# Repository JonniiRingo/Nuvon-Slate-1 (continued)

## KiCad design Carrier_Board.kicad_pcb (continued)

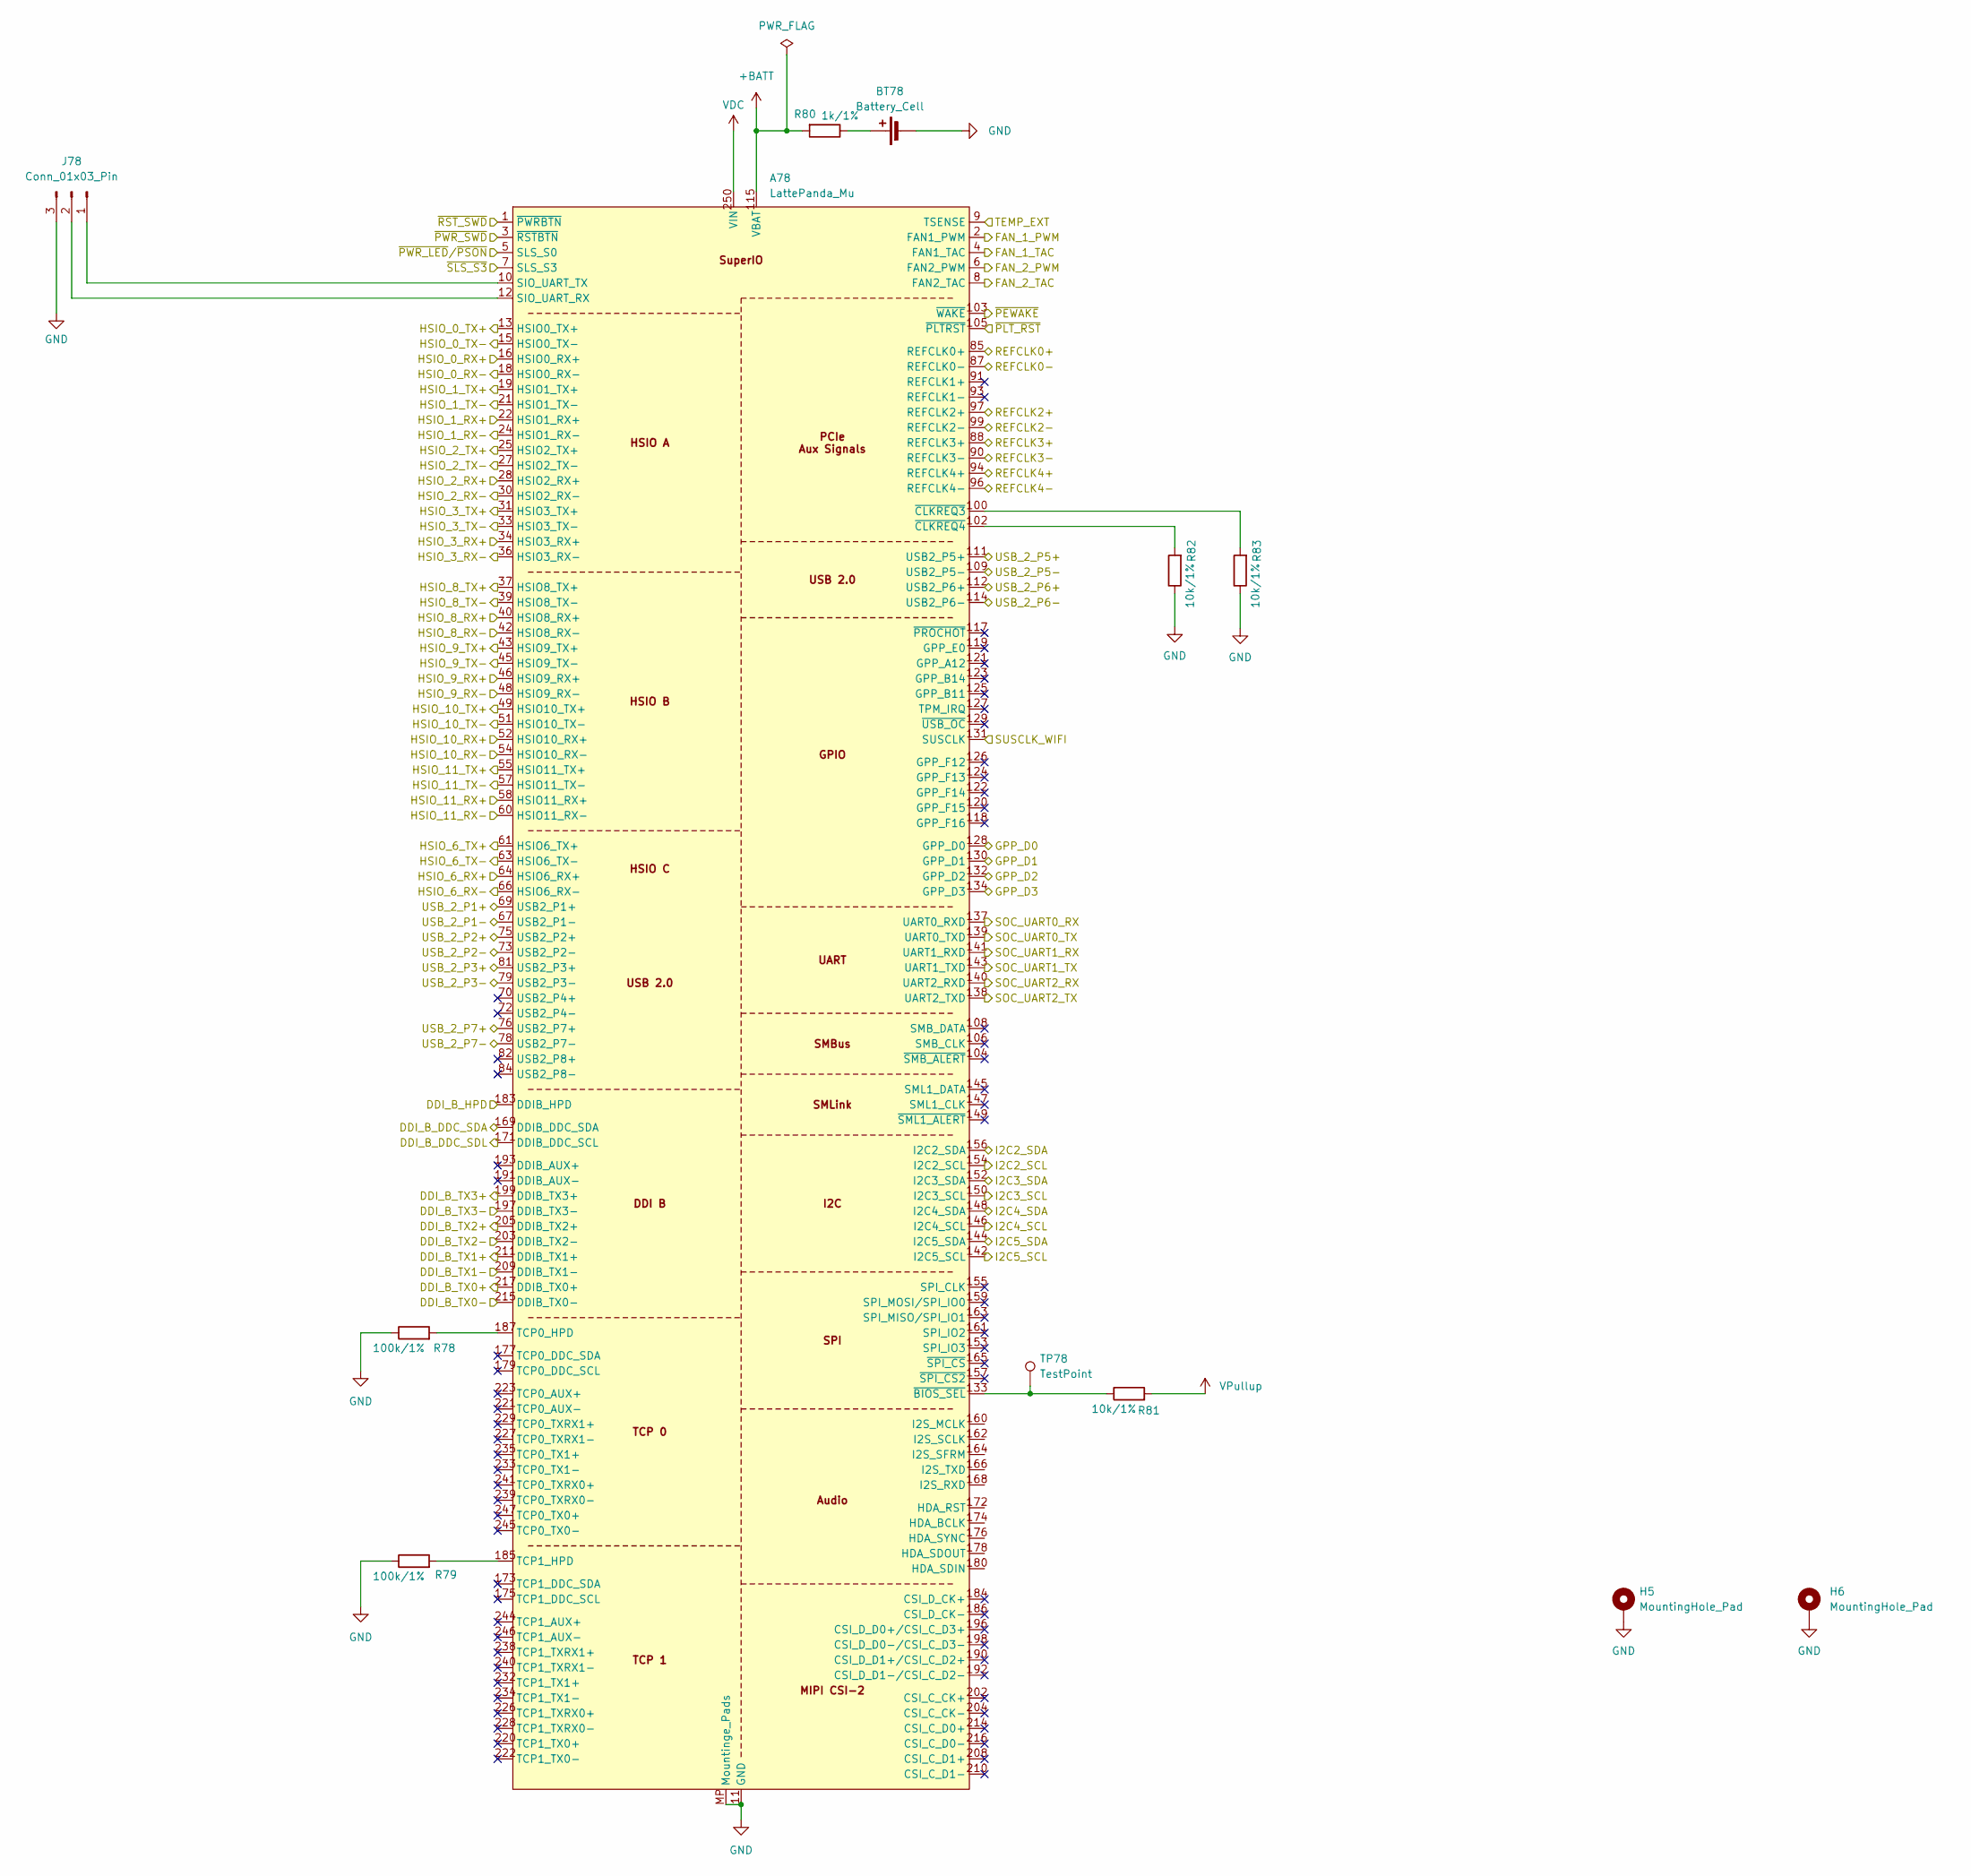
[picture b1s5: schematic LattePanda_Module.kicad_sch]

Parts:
A78: LattePanda_Mu; LattePanda_Module_H8.0mm_Horizontal
BT78: Battery_Cell; Battery_Holder_CR1220_S8411-45R
H5, H6: MountingHole_Pad; MountingHole_3mm_M2_Pad_TopOnly
J78: Conn_01x03_Pin; PinHeader_1x03_P2.54mm_Vertical
R78, R79: 100k/1%; R_0402_1005Metric
R80: 1k/1%; R_0402_1005Metric
R81, R82, R83: 10k/1%; R_0402_1005Metric
TP78: TestPoint; TestPoint_Pad_D1.5mm

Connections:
+BATT: A78.115 (VBAT), R80.2
/Fan/FAN_1_PWM: A78.4 (FAN1_TAC); also elsewhere on the board
/Fan/FAN_1_TAC: A78.2 (FAN1_PWM); also elsewhere on the board
/Fan/FAN_2_PWM: A78.8 (FAN2_TAC); also elsewhere on the board
/Fan/FAN_2_TAC: A78.6 (FAN2_PWM); also elsewhere on the board
/Fan/TEMP: A78.9 (TSENSE); also elsewhere on the board
/GPIO/GPP_D0: A78.128 (GPP_D0); also elsewhere on the board
/GPIO/GPP_D1: A78.130 (GPP_D1); also elsewhere on the board
/GPIO/GPP_D2: A78.132 (GPP_D2); also elsewhere on the board
/GPIO/GPP_D3: A78.134 (GPP_D3); also elsewhere on the board
/GPIO/I2C2_SCL: A78.154 (I2C2_SCL); also elsewhere on the board
/GPIO/I2C2_SDA: A78.156 (I2C2_SDA); also elsewhere on the board
/GPIO/I2C3_SCL: A78.150 (I2C3_SCL); also elsewhere on the board
/GPIO/I2C3_SDA: A78.152 (I2C3_SDA); also elsewhere on the board
/GPIO/I2C4_SCL: A78.146 (I2C4_SCL); also elsewhere on the board
/GPIO/I2C4_SDA: A78.148 (I2C4_SDA); also elsewhere on the board
/GPIO/I2C5_SCL: A78.142 (I2C5_SCL); also elsewhere on the board
/GPIO/I2C5_SDA: A78.144 (I2C5_SDA); also elsewhere on the board
/GPIO/SOC_UART0_RX: A78.137 (UART0_RXD); also elsewhere on the board
/GPIO/SOC_UART0_TX: A78.139 (UART0_TXD); also elsewhere on the board
/GPIO/SOC_UART1_RX: A78.141 (UART1_RXD); also elsewhere on the board
/GPIO/SOC_UART1_TX: A78.143 (UART1_TXD); also elsewhere on the board
/GPIO/SOC_UART2_RX: A78.140 (UART2_RXD); also elsewhere on the board
/GPIO/SOC_UART2_TX: A78.138 (UART2_TXD); also elsewhere on the board
/Gigabit Ethernet/GbE_PCIe_CLK+: A78.94 (REFCLK4+); also elsewhere on the board
/Gigabit Ethernet/GbE_PCIe_CLK-: A78.96 (REFCLK4-); also elsewhere on the board
/Gigabit Ethernet/GbE_PCIe_RX+: A78.64 (HSIO6_RX+); also elsewhere on the board
/Gigabit Ethernet/GbE_PCIe_RX-: A78.66 (HSIO6_RX-); also elsewhere on the board
/Gigabit Ethernet/GbE_PCIe_TX+: A78.61 (HSIO6_TX+); also elsewhere on the board
/Gigabit Ethernet/GbE_PCIe_TX-: A78.63 (HSIO6_TX-); also elsewhere on the board
/HDMI/DDI_B_HPD: A78.183 (DDIB_HPD); also elsewhere on the board
/HDMI/DDI_B_TX0+: A78.217 (DDIB_TX0+); also elsewhere on the board
/HDMI/DDI_B_TX0-: A78.215 (DDIB_TX0-); also elsewhere on the board
/HDMI/DDI_B_TX1+: A78.211 (DDIB_TX1+); also elsewhere on the board
/HDMI/DDI_B_TX1-: A78.209 (DDIB_TX1-); also elsewhere on the board
/HDMI/DDI_B_TX2+: A78.205 (DDIB_TX2+); also elsewhere on the board
/HDMI/DDI_B_TX2-: A78.203 (DDIB_TX2-); also elsewhere on the board
/HDMI/DDI_B_TX3+: A78.199 (DDIB_TX3+); also elsewhere on the board
/HDMI/DDI_B_TX3-: A78.197 (DDIB_TX3-); also elsewhere on the board
/HDMI/DDI_DDC_SCA: A78.169 (DDIB_DDC_SDA); also elsewhere on the board
/HDMI/DDI_DDC_SCL: A78.171 (DDIB_DDC_SCL); also elsewhere on the board
/LattePanda Module/HSIO_0_TX+: A78.13 (HSIO0_TX+); also elsewhere on the board
/LattePanda Module/HSIO_0_TX-: A78.15 (HSIO0_TX-); also elsewhere on the board
/LattePanda Module/HSIO_1_TX+: A78.19 (HSIO1_TX+); also elsewhere on the board
/LattePanda Module/HSIO_1_TX-: A78.21 (HSIO1_TX-); also elsewhere on the board
/LattePanda Module/HSIO_2_RX+: A78.28 (HSIO2_RX+); also elsewhere on the board
/LattePanda Module/HSIO_2_RX-: A78.30 (HSIO2_RX-); also elsewhere on the board
/LattePanda Module/HSIO_2_TX+: A78.25 (HSIO2_TX+); also elsewhere on the board
/LattePanda Module/HSIO_2_TX-: A78.27 (HSIO2_TX-); also elsewhere on the board
/LattePanda Module/HSIO_3_RX+: A78.34 (HSIO3_RX+); also elsewhere on the board
/LattePanda Module/HSIO_3_RX-: A78.36 (HSIO3_RX-); also elsewhere on the board
/LattePanda Module/HSIO_3_TX+: A78.31 (HSIO3_TX+); also elsewhere on the board
/LattePanda Module/HSIO_3_TX-: A78.33 (HSIO3_TX-); also elsewhere on the board
/LattePanda Module/HSIO_8_RX+: A78.40 (HSIO8_RX+); also elsewhere on the board
/LattePanda Module/HSIO_8_RX-: A78.42 (HSIO8_RX-); also elsewhere on the board
/LattePanda Module/HSIO_8_TX+: A78.37 (HSIO8_TX+); also elsewhere on the board
/LattePanda Module/HSIO_8_TX-: A78.39 (HSIO8_TX-); also elsewhere on the board
/LattePanda Module/HSIO_9_RX+: A78.46 (HSIO9_RX+); also elsewhere on the board
/LattePanda Module/HSIO_9_RX-: A78.48 (HSIO9_RX-); also elsewhere on the board
/LattePanda Module/HSIO_9_TX+: A78.43 (HSIO9_TX+); also elsewhere on the board
/LattePanda Module/HSIO_9_TX-: A78.45 (HSIO9_TX-); also elsewhere on the board
/LattePanda Module/HSIO_10_RX+: A78.52 (HSIO10_RX+); also elsewhere on the board
/LattePanda Module/HSIO_10_RX-: A78.54 (HSIO10_RX-); also elsewhere on the board
/LattePanda Module/HSIO_10_TX+: A78.49 (HSIO10_TX+); also elsewhere on the board
/LattePanda Module/HSIO_10_TX-: A78.51 (HSIO10_TX-); also elsewhere on the board
/LattePanda Module/HSIO_11_RX+: A78.58 (HSIO11_RX+); also elsewhere on the board
/LattePanda Module/HSIO_11_RX-: A78.60 (HSIO11_RX-); also elsewhere on the board
/LattePanda Module/HSIO_11_TX+: A78.55 (HSIO11_TX+); also elsewhere on the board
/LattePanda Module/HSIO_11_TX-: A78.57 (HSIO11_TX-); also elsewhere on the board
/LattePanda Module/REFCLK0+: A78.85 (REFCLK0+); also elsewhere on the board
/LattePanda Module/REFCLK0-: A78.87 (REFCLK0-); also elsewhere on the board
/LattePanda Module/REFCLK2+: A78.97 (REFCLK2+); also elsewhere on the board
/LattePanda Module/REFCLK2-: A78.99 (REFCLK2-); also elsewhere on the board
/LattePanda Module/REFCLK3+: A78.88 (REFCLK3+); also elsewhere on the board
/LattePanda Module/REFCLK3-: A78.90 (REFCLK3-); also elsewhere on the board
/LattePanda Module/SUSCLK_WIFI: A78.131 (SUSCLK); also elsewhere on the board
/LattePanda Module/USB_2_P6+: A78.112 (USB2_P6+)
/LattePanda Module/USB_2_P6-: A78.114 (USB2_P6-)
/LattePanda Module/USB_2_P7+: A78.76 (USB2_P7+); also elsewhere on the board
/LattePanda Module/USB_2_P7-: A78.78 (USB2_P7-); also elsewhere on the board
/LattePanda Module/~PWR_LED/~PSON: A78.5 (SLS_S0); also elsewhere on the board
/LattePanda Module/~PWR_SWD: A78.3 (~RSTBTN); also elsewhere on the board
/LattePanda Module/~RST_SWD: A78.1 (~PWRBTN); also elsewhere on the board
/USB 2.0 & 3.0/CON_USB1_D_N: A78.109 (USB2_P5-); also elsewhere on the board
/USB 2.0 & 3.0/CON_USB1_D_P: A78.111 (USB2_P5+); also elsewhere on the board
/USB 2.0 & 3.0/CON_USB2_D_N: A78.79 (USB2_P3-); also elsewhere on the board
/USB 2.0 & 3.0/CON_USB2_D_P: A78.81 (USB2_P3+); also elsewhere on the board
/USB 2.0 & 3.0/CON_USB3_D_N: A78.73 (USB2_P2-); also elsewhere on the board
/USB 2.0 & 3.0/CON_USB3_D_P: A78.75 (USB2_P2+); also elsewhere on the board
/USB 2.0 & 3.0/CON_USB3_SSRX_N: A78.18 (HSIO0_RX-); also elsewhere on the board
/USB 2.0 & 3.0/CON_USB3_SSRX_P: A78.16 (HSIO0_RX+); also elsewhere on the board
/USB 2.0 & 3.0/CON_USB4_D_N: A78.67 (USB2_P1-); also elsewhere on the board
/USB 2.0 & 3.0/CON_USB4_D_P: A78.69 (USB2_P1+); also elsewhere on the board
/USB 2.0 & 3.0/CON_USB4_SSRX_N: A78.24 (HSIO1_RX-); also elsewhere on the board
/USB 2.0 & 3.0/CON_USB4_SSRX_P: A78.22 (HSIO1_RX+); also elsewhere on the board
/~PLT_RST: A78.105 (~PLTRST); also elsewhere on the board
/~PWR_LED/~PSON: A78.7 (SLS_S3); also elsewhere on the board
/~WAKE: A78.103 (~WAKE); also elsewhere on the board
GND: A78.11 (GND), A78.14 (GND), A78.17 (GND), A78.20 (GND), A78.23 (GND), A78.26 (GND), A78.29 (GND), A78.32 (GND), A78.35 (GND), A78.38 (GND), A78.41 (GND), A78.44 (GND), A78.47 (GND), A78.50 (GND), A78.53 (GND), A78.56 (GND), A78.59 (GND), A78.62 (GND), A78.65 (GND), A78.68 (GND), A78.71 (GND), A78.74 (GND), A78.77 (GND), A78.80 (GND), A78.83 (GND), A78.86 (GND), A78.89 (GND), A78.92 (GND), A78.95 (GND), A78.98 (GND), A78.101 (GND), A78.107 (GND), A78.110 (GND), A78.113 (GND), A78.116 (GND), A78.135 (GND), A78.136 (GND), A78.151 (GND), A78.158 (GND), A78.167 (GND), A78.170 (GND), A78.181 (GND), A78.182 (GND), A78.188 (GND), A78.189 (GND), A78.194 (GND), A78.195 (GND), A78.200 (GND), A78.201 (GND), A78.206 (GND), A78.207 (GND), A78.212 (GND), A78.213 (GND), A78.218 (GND), A78.219 (GND), A78.224 (GND), A78.225 (GND), A78.230 (GND), A78.231 (GND), A78.236 (GND), A78.237 (GND), A78.242 (GND), A78.243 (GND), A78.248 (GND), A78.249 (GND), A78.MP (Mountinge_Pads), BT78.2 (-), H5.1 (1_1), H6.1 (1_1), J78.3, R78.1, R79.1, R82.1, R83.1; also elsewhere on the board
unnamed: A78.12 (SIO_UART_RX), J78.2
unnamed: A78.10 (SIO_UART_TX), J78.1
unnamed: A78.187 (TCP0_HPD), R78.2
unnamed: A78.185 (TCP1_HPD), R79.2
unnamed: A78.133 (~BIOS_SEL), R81.1, TP78.1 (1_1)
unnamed: A78.100 (~CLKREQ3), R83.2
unnamed: A78.102 (~CLKREQ4), R82.2
unnamed: BT78.1 (+), R80.1
VDC: A78.250 (VIN), A78.251 (VIN), A78.252 (VIN), A78.253 (VIN), A78.254 (VIN), A78.255 (VIN), A78.256 (VIN), A78.257 (VIN), A78.258 (VIN), A78.259 (VIN), A78.260 (VIN); also elsewhere on the board
VPullup: R81.2; also elsewhere on the board

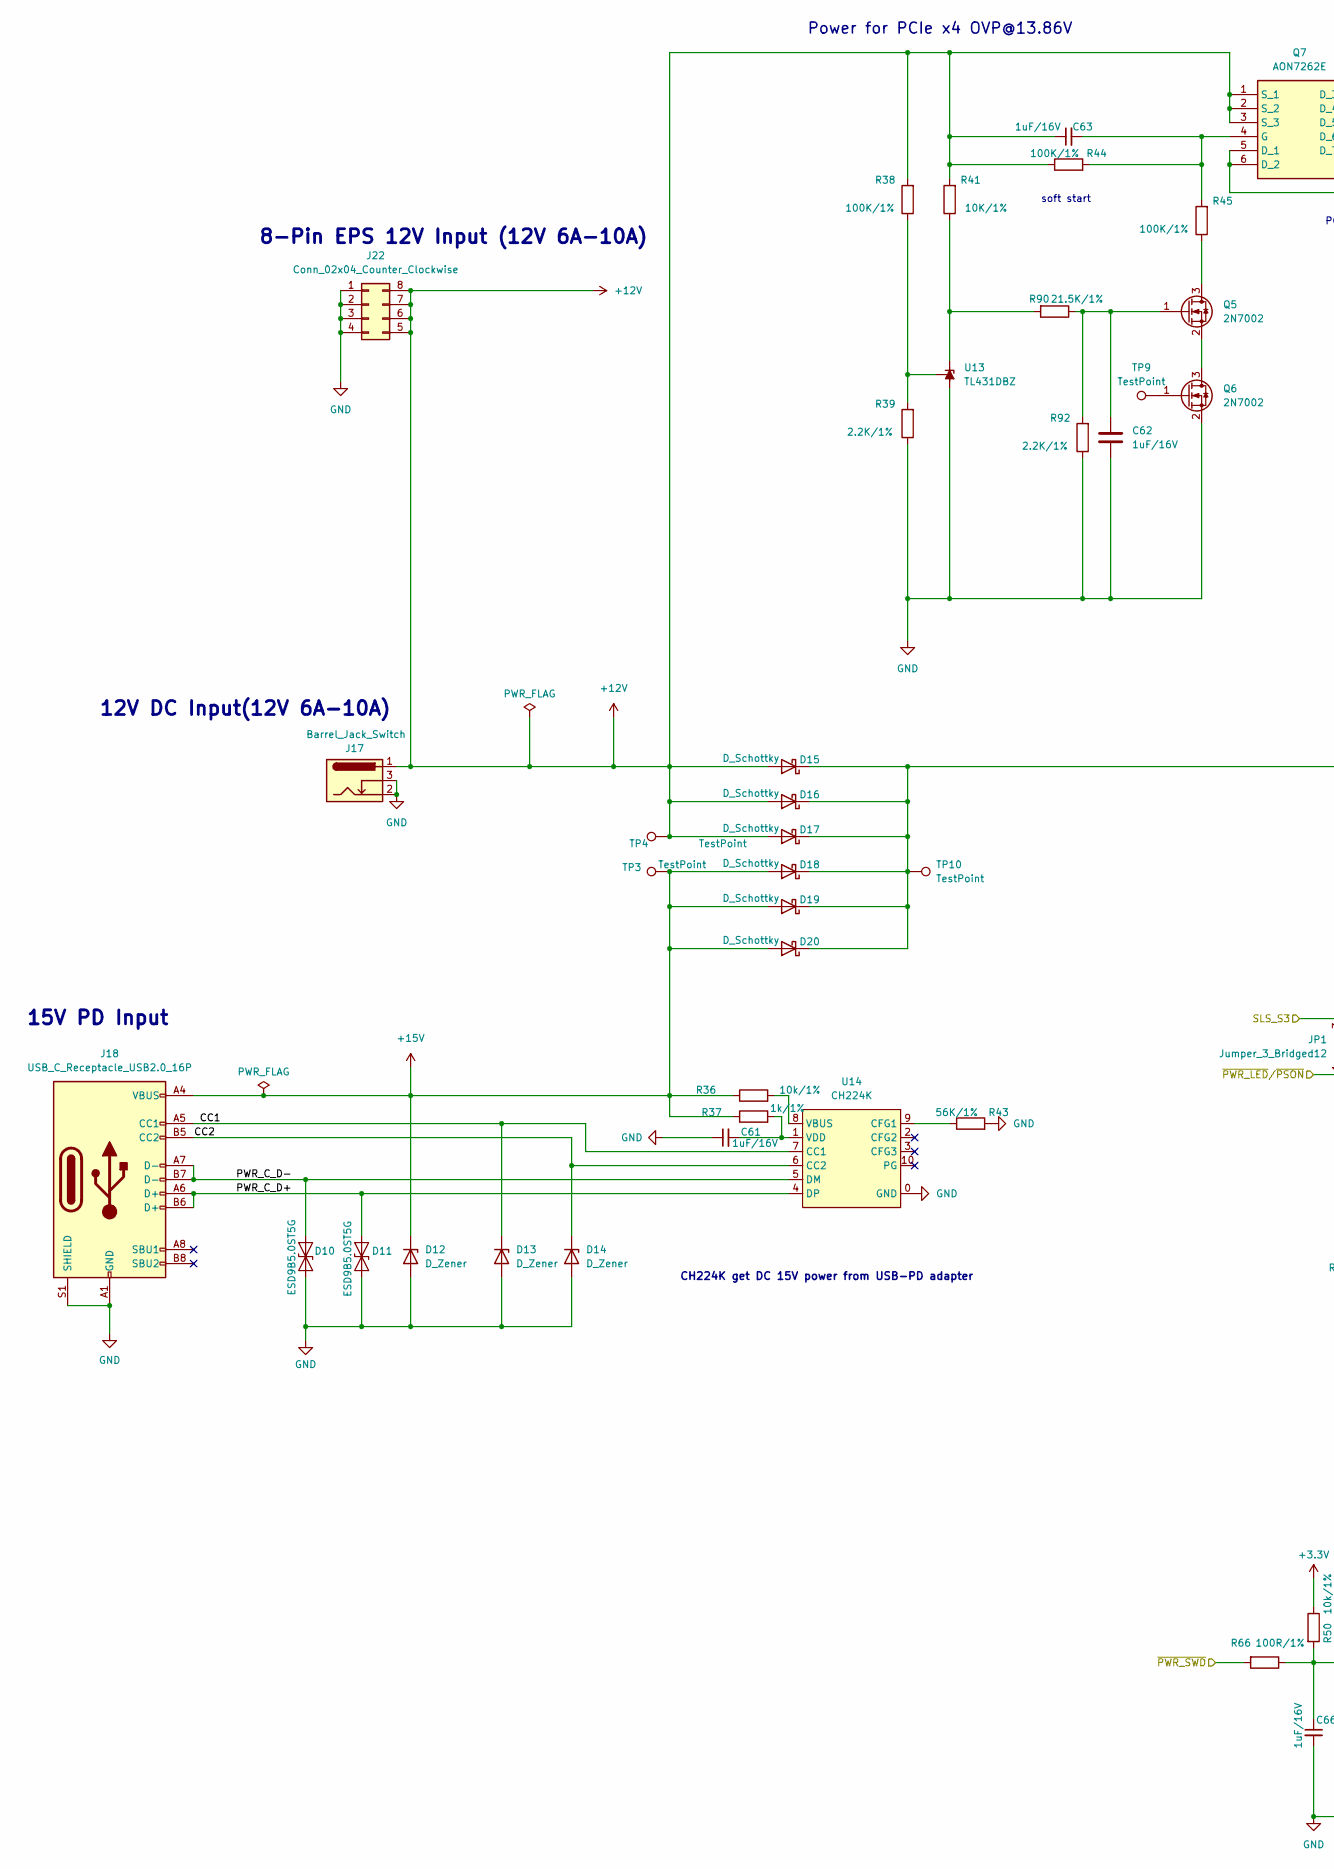
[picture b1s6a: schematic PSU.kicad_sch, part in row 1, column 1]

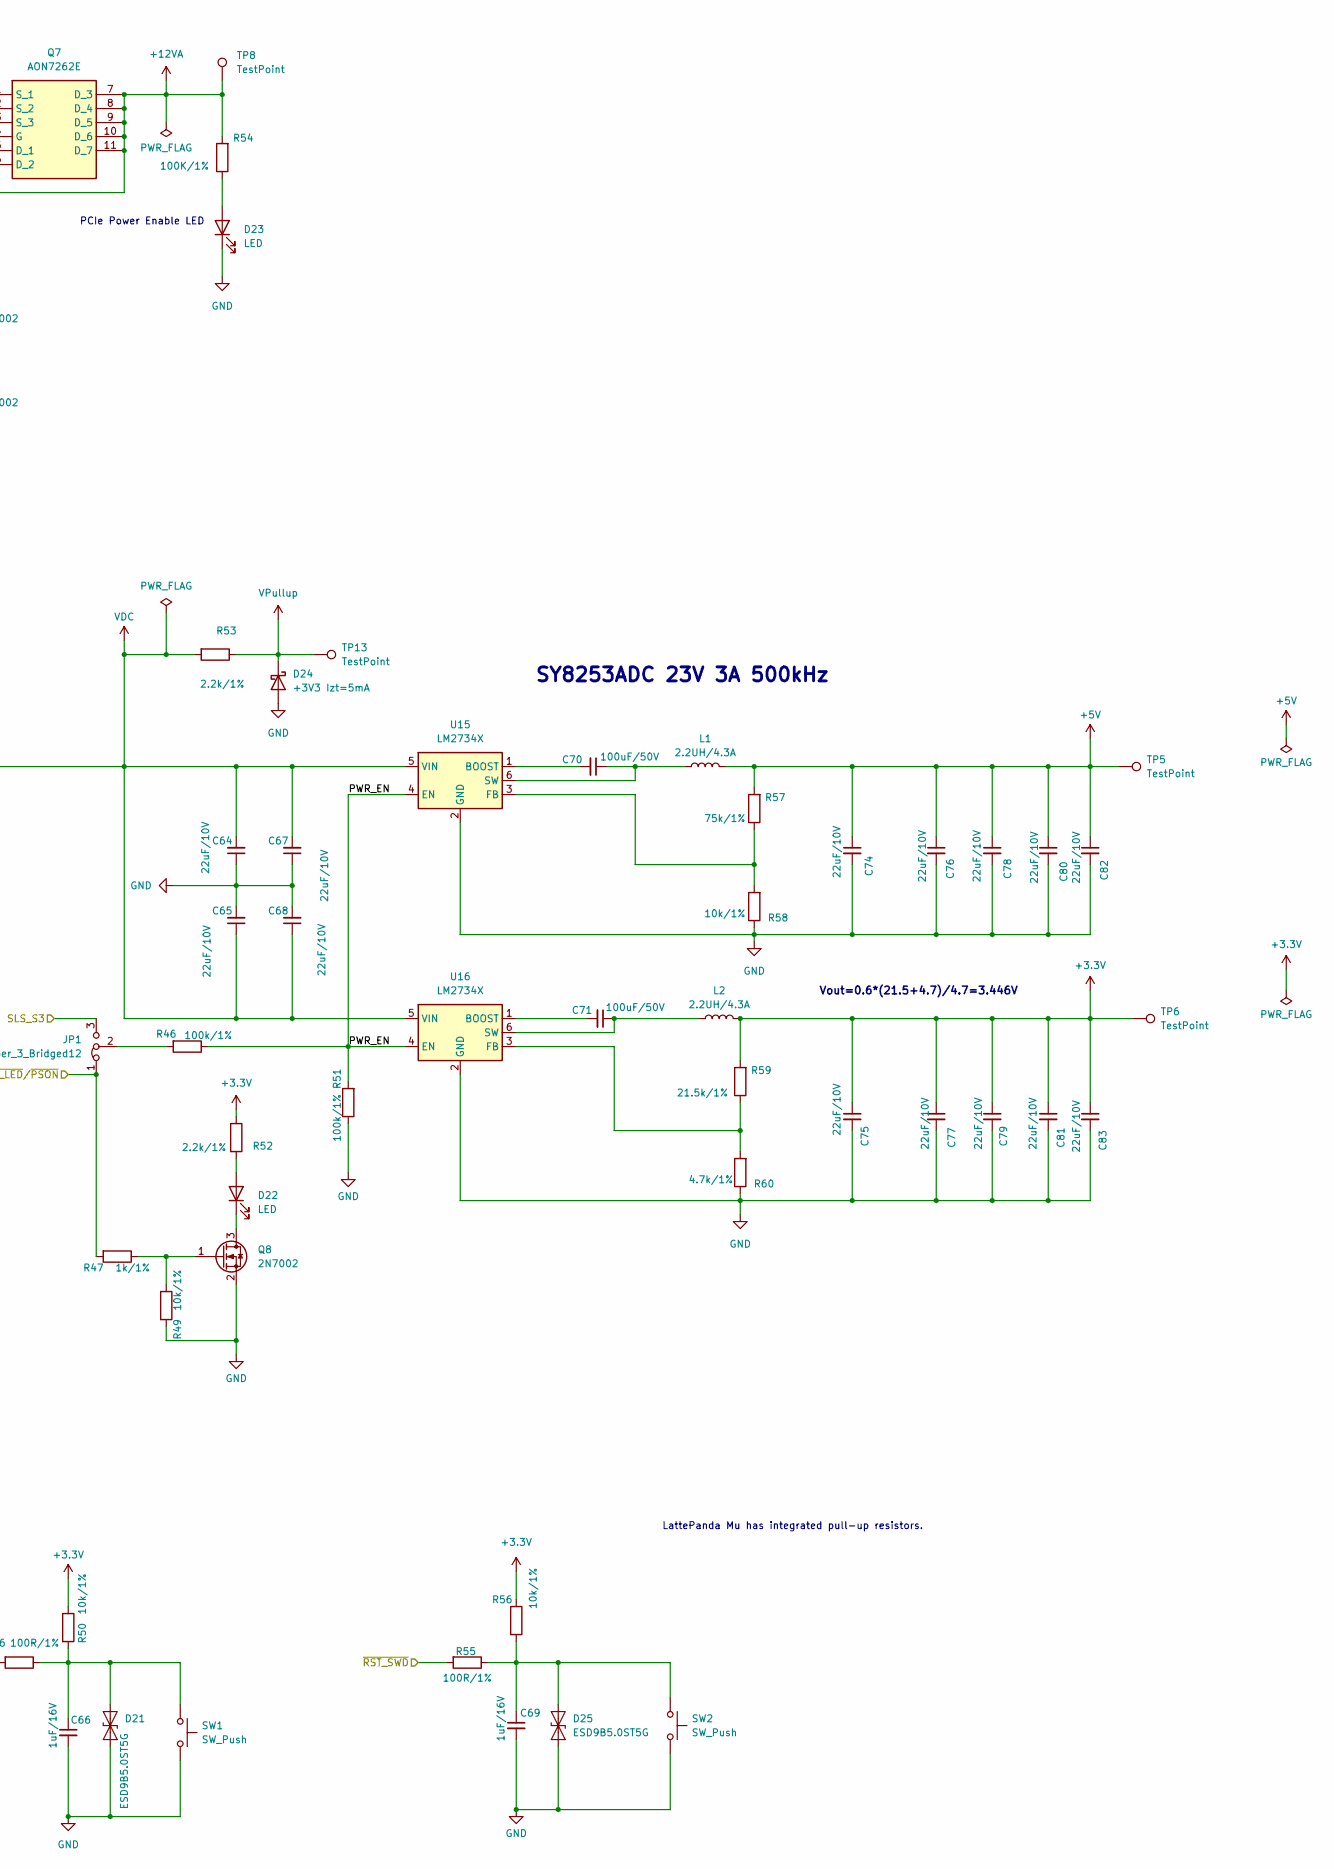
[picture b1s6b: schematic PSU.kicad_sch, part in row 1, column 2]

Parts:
C61, C62, C63, C66, C69: 1uF/16V; C_0402_1005Metric
C64, C65, C67, C68, C74, C75, C76, C77, C78, C79, C80, C81, C82, C83: 22uF/10V; C_0603_1608Metric
C70, C71: 100uF/50V; C_0603_1608Metric
D10, D11, D21, D25: ESD9B5.0ST5G; D_0402_1005Metric
D12, D13, D14: D_Zener; D_0402_1005Metric
D15, D16, D17, D18, D19, D20: D_Schottky; D_SMA
D22, D23: LED; LED_0603_1608Metric
D24: +3V3 Izt=5mA; D_SOD-323
J17: Barrel_Jack_Switch; DC_Jack_DC007B_30V_10A
J18: USB_C_Receptacle_USB2.0_16P; USB_C_Receptacle_G-Switch_GT-USB-7010ASV
J22: Conn_02x04_Counter_Clockwise; CONN_5569-08A_MOL
JP1: Jumper_3_Bridged12; PinHeader_1x03_P2.54mm_Vertical
L1, L2: 2.2UH/4.3A; L_Sunlord_SWPA4020S
Q5, Q6, Q8: 2N7002; SOT-23
Q7: AON7262E; MOSFET_PDFN8_3.3x3.3
R36, R49, R50, R56, R58: 10k/1%; R_0402_1005Metric
R37, R47: 1k/1%; R_0402_1005Metric
R38, R44, R45, R54: 100K/1%; R_0402_1005Metric
R39, R92: 2.2K/1%; R_0402_1005Metric
R41: 10K/1%; R_0402_1005Metric
R43: 56K/1%; R_0402_1005Metric
R46, R51: 100k/1%; R_0402_1005Metric
R52, R53: 2.2k/1%; R_0402_1005Metric
R55, R66: 100R/1%; R_0402_1005Metric
R57: 75k/1%; R_0402_1005Metric
R59: 21.5k/1%; R_0402_1005Metric
R60: 4.7k/1%; R_0402_1005Metric
R90: 21.5K/1%; R_0402_1005Metric
SW1, SW2: SW_Push; SW_Push_6x6x6
TP3, TP4, TP5, TP6, TP8, TP9, TP10, TP13: TestPoint; TestPoint_Pad_D1.5mm
U13: TL431DBZ; SOT-23
U14: CH224K; ESSOP-10-1EP_3.9x5mm_P1.0mm_EP3.2x2.3
U15, U16: LM2734X; TSOT-23-6

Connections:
+3.3V: C75.1, C77.1, C79.1, C81.1, C83.1, L2.2, R50.1, R52.1, R56.1, R59.2, TP6.1 (1_1); also elsewhere on the board
+5V: C74.1, C76.1, C78.1, C80.1, C82.1, L1.2, R57.2, TP5.1 (1_1); also elsewhere on the board
+12V: C63.1, D15.2 (A), D16.2 (A), D17.2 (A), J17.1, J22.5, J22.6, J22.7, J22.8, Q7.1 (S_1), Q7.2 (S_2), Q7.3 (S_3), R38.2, R41.2, R44.1, TP4.1 (1_1); also elsewhere on the board
+12VA: Q7.5 (D_1), Q7.6 (D_2), Q7.7 (D_3), Q7.8 (D_4), Q7.9 (D_5), Q7.10 (D_6), Q7.11 (D_7), R54.2, TP8.1 (1_1); also elsewhere on the board
+15V: D12.1 (K), D18.2 (A), D19.2 (A), D20.2 (A), J18.A4 (VBUS), J18.A9 (VBUS), J18.B4 (VBUS), J18.B9 (VBUS), R36.1, R37.1, TP3.1 (1_1)
/LattePanda Module/~PWR_LED/~PSON: JP1.3 (B); also elsewhere on the board
/LattePanda Module/~PWR_SWD: R66.2; also elsewhere on the board
/LattePanda Module/~RST_SWD: R55.2; also elsewhere on the board
/PSU/CC1: D13.1 (K), J18.A5 (CC1), U14.7 (CC1)
/PSU/CC2: D14.1 (K), J18.B5 (CC2), U14.6 (CC2)
/PSU/PWR_C_D+: D11.2 (A2), J18.A6 (D+), J18.B6 (D+), U14.4 (DP)
/PSU/PWR_C_D-: D10.2 (A2), J18.A7 (D-), J18.B7 (D-), U14.5 (DM)
/PSU/PWR_EN: R46.1, R51.2, U15.4 (EN), U16.4 (EN)
/~PWR_LED/~PSON: JP1.1 (A), R47.2; also elsewhere on the board
GND: C61.1, C62.2, C64.1, C65.2, C66.2, C67.1, C68.2, C69.2, C74.2, C75.2, C76.2, C77.2, C78.2, C79.2, C80.2, C81.2, C82.2, C83.2, D10.1 (A1), D11.1 (A1), D12.2 (A), D13.2 (A), D14.2 (A), D21.1 (A1), D23.1 (K), D24.2 (A), D25.1 (A1), J17.2, J17.3, J18.A1 (GND), J18.A12 (GND), J18.B1 (GND), J18.B12 (GND), J18.S1 (SHIELD), J22.1, J22.2, J22.3, J22.4, Q6.2 (S), Q8.2 (S), R39.1, R43.2, R49.2, R51.1, R58.1, R60.1, R92.1, SW1.2, SW2.2, U13.3 (A), U14.0 (GND), U15.2 (GND), U16.2 (GND); also elsewhere on the board
unnamed: C66.1, D21.2 (A2), R50.2, R66.1, SW1.1
unnamed: D22.2 (A), R52.2
unnamed: D22.1 (K), Q8.3 (D)
unnamed: D23.2 (A), R54.1
unnamed: C69.1, D25.2 (A2), R55.1, R56.2, SW2.1
unnamed: JP1.2 (C), R46.2
unnamed: Q5.3 (D), R45.1
unnamed: C62.1, Q5.1 (G), R90.1, R92.2
unnamed: Q5.2 (S), Q6.3 (D)
unnamed: Q6.1 (G), TP9.1 (1_1)
unnamed: C63.2, Q7.4 (G), R44.2, R45.2
unnamed: Q8.1 (G), R47.1, R49.1
unnamed: R41.1, R90.2, U13.1 (K)
unnamed: R38.1, R39.2, U13.2 (REF)
unnamed: R43.1, U14.9 (CFG1)
unnamed: R36.2, U14.8 (VBUS)
unnamed: C61.2, R37.2, U14.1 (VDD)
unnamed: C70.2, U15.1 (BOOST)
unnamed: R57.1, R58.2, U15.3 (FB)
unnamed: C70.1, L1.1, U15.6 (SW)
unnamed: C71.2, U16.1 (BOOST)
unnamed: R59.1, R60.2, U16.3 (FB)
unnamed: C71.1, L2.1, U16.6 (SW)
VDC: C64.2, C65.1, C67.2, C68.1, D15.1 (K), D16.1 (K), D17.1 (K), D18.1 (K), D19.1 (K), D20.1 (K), R53.2, TP10.1 (1_1), U15.5 (VIN), U16.5 (VIN); also elsewhere on the board
VPullup: D24.1 (K), R53.1, TP13.1 (1_1); also elsewhere on the board

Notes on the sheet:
soft start
15V PD Input
8-Pin EPS 12V Input (12V 6A-10A)
Vout=0.6*(21.5+4.7)/4.7=3.446V
SY8253ADC 23V 3A 500kHz
PCIe Power Enable LED
Power for PCIe x4 OVP@13.86V
CH224K get DC 15V power from USB-PD adapter
12V DC Input(12V 6A-10A)
LattePanda Mu has integrated pull-up resistors.

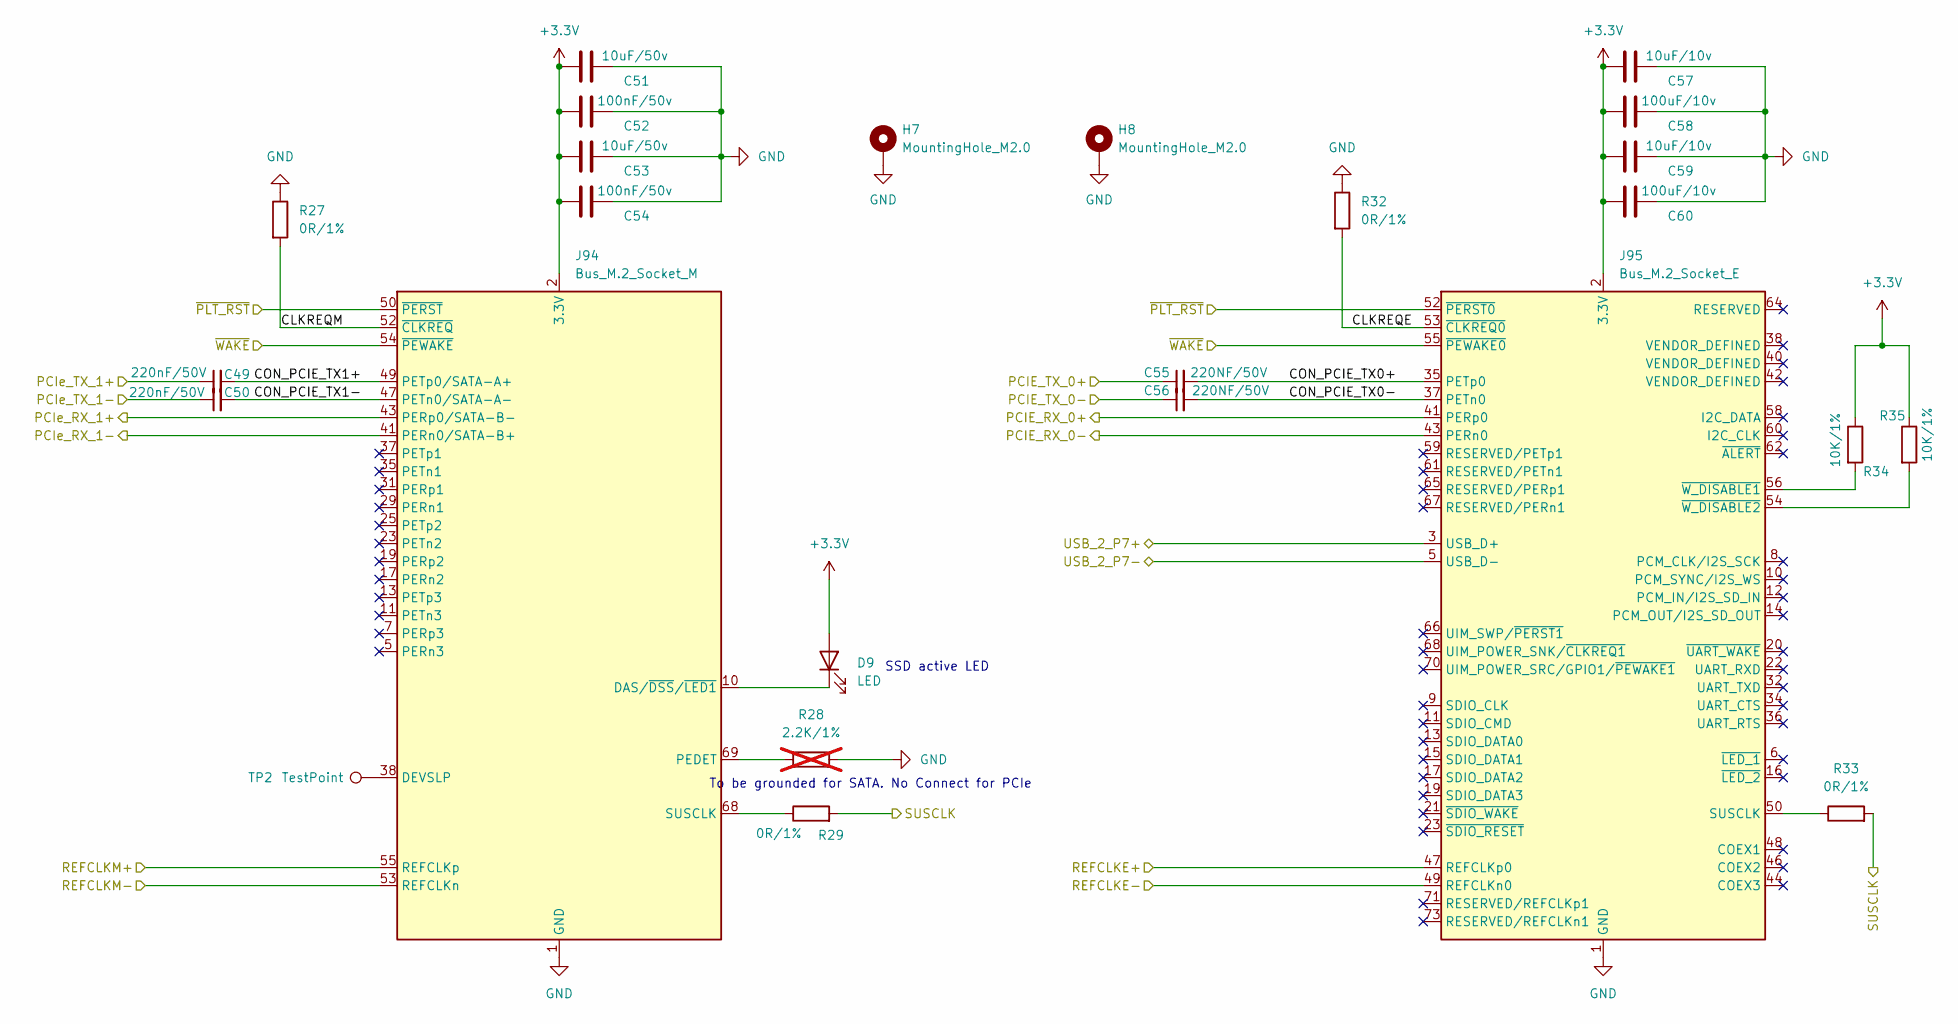
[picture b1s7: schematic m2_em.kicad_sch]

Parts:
C49, C50: 220nF/50V; C_0402_1005Metric
C51, C53: 10uF/50v; C_0402_1005Metric
C52, C54: 100nF/50v; C_0402_1005Metric
C55, C56: 220NF/50V; C_0402_1005Metric
C57, C59: 10uF/10v; C_0402_1005Metric
C58, C60: 100uF/10v; C_0402_1005Metric
D9: LED; LED_0603
H7, H8: MountingHole_M2.0; MountingHole_3.2mm_M3_Pad_Via
J94: Bus_M.2_Socket_M; PCIe_M.2_Connectors_P=0.5mm_H=4.2mm_KeyM
J95: Bus_M.2_Socket_E; PCIe_M.2_Connectors_P=0.5mm_H=4.2mm_KeyE
R27, R29, R32, R33: 0R/1%; R_0402_1005Metric
R28: 2.2K/1%; R_0402_1005Metric; not fitted
R34, R35: 10K/1%; R_0402_1005Metric
TP2: TestPoint; TestPoint_Pad_D1.5mm

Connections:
+3.3V: C51.1, C52.1, C53.1, C54.1, C57.1, C58.1, C59.1, C60.1, D9.2 (A), J94.2 (3.3V), J94.4 (3.3V), J94.12 (3.3V), J94.14 (3.3V), J94.16 (3.3V), J94.18 (3.3V), J94.70 (3.3V), J94.72 (3.3V), J94.74 (3.3V), J95.2 (3.3V), J95.4 (3.3V), J95.72 (3.3V), J95.74 (3.3V), R34.1, R35.1; also elsewhere on the board
/LattePanda Module/HSIO_2_TX+: C49.1; also elsewhere on the board
/LattePanda Module/HSIO_2_TX-: C50.1; also elsewhere on the board
/LattePanda Module/HSIO_3_TX+: C55.1; also elsewhere on the board
/LattePanda Module/HSIO_3_TX-: C56.1; also elsewhere on the board
/LattePanda Module/SUSCLK_WIFI: R29.2, R33.2; also elsewhere on the board
/M.2 M Key/CLKREQE: J95.53 (~CLKREQ0), R32.2; also elsewhere on the board
/M.2 M Key/CLKREQM: J94.52 (~CLKREQ), R27.2; also elsewhere on the board
/M.2 M Key/CON_PCIE_TX0+: C55.2, J95.35 (PETp0); also elsewhere on the board
/M.2 M Key/CON_PCIE_TX0-: C56.2, J95.37 (PETn0); also elsewhere on the board
/M.2 M Key/CON_PCIE_TX1+: C49.2, J94.49 (PETp0/SATA-A+); also elsewhere on the board
/M.2 M Key/CON_PCIE_TX1-: C50.2, J94.47 (PETn0/SATA-A-); also elsewhere on the board
GND: C51.2, C52.2, C53.2, C54.2, C57.2, C58.2, C59.2, C60.2, H7.1 (1_1), H8.1 (1_1), J94.1 (GND), J94.3 (GND), J94.9 (GND), J94.15 (GND), J94.21 (GND), J94.27 (GND), J94.33 (GND), J94.39 (GND), J94.45 (GND), J94.51 (GND), J94.57 (GND), J94.71 (GND), J94.73 (GND), J94.75 (GND), J95.1 (GND), J95.7 (GND), J95.18 (GND), J95.33 (GND), J95.39 (GND), J95.45 (GND), J95.51 (GND), J95.57 (GND), J95.63 (GND), J95.69 (GND), J95.75 (GND), R27.1, R28.2, R32.1; also elsewhere on the board
unnamed 158: D9.1 (K), J94.10 (DAS/~DSS/~LED1); also elsewhere on the board
unnamed 175: J94.38 (DEVSLP), TP2.1 (1_1); also elsewhere on the board
unnamed 176: J94.69 (PEDET), R28.1; also elsewhere on the board
unnamed 177: J94.68 (SUSCLK), R29.1; also elsewhere on the board
unnamed 178: J95.50 (SUSCLK), R33.1; also elsewhere on the board
unnamed 179: J95.56 (~W_DISABLE1), R34.2; also elsewhere on the board
unnamed 180: J95.54 (~W_DISABLE2), R35.2; also elsewhere on the board
unnamed: J94.50 (~PERST), J95.52 (~PERST0)
unnamed: J94.54 (~PEWAKE), J95.55 (~PEWAKE0)

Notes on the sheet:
SSD active LED
To be grounded for SATA. No Connect for PCIe
